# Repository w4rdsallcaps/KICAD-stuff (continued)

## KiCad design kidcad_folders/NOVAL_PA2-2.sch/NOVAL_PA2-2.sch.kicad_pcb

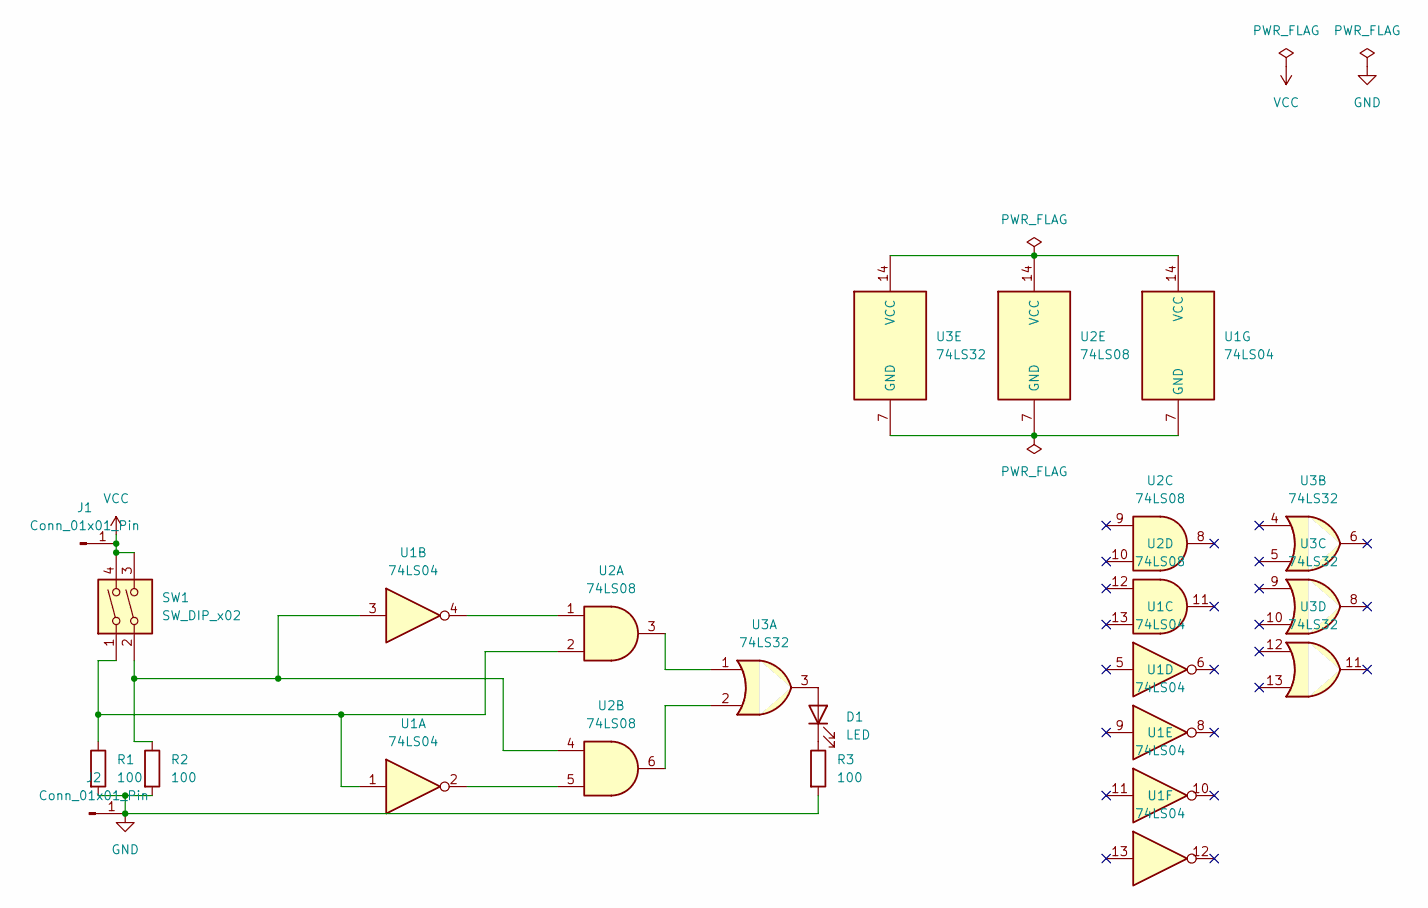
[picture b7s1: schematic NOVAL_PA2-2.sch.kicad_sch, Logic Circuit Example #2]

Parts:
D1: LED; LED_2512_6332Metric_Pad1.52x3.35mm_HandSolder
J1, J2: Conn_01x01_Pin; MountingHole_2.2mm_M2_DIN965_Pad
R1, R2, R3: 100; R_0508_1220Metric
SW1: SW_DIP_x02; SW_DIP_SPSTx02_Slide_9.78x7.26mm_W7.62mm_P2.54mm
U1: 74LS04; SOIC-14_3.9x8.7mm_P1.27mm
U2: 74LS08; SOIC-14_3.9x8.7mm_P1.27mm
U3: 74LS32; SOIC-14_3.9x8.7mm_P1.27mm

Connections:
GND: J2.1 (Pin_1_1), R1.2, R2.2, R3.2
unnamed: D1.2 (A), U3.3
unnamed: D1.1 (K), R3.1
unnamed: R1.1, SW1.1, U1.1, U2.2
unnamed: R2.1, SW1.2, U1.3, U2.4
unnamed: U1.2, U2.5
unnamed: U1.4, U2.1
unnamed: U1.7 (GND), U2.7 (GND), U3.7 (GND)
unnamed: U1.14 (VCC), U2.14 (VCC), U3.14 (VCC)
unnamed: U2.3, U3.1
unnamed: U2.6, U3.2
VCC: J1.1 (Pin_1_1), SW1.3, SW1.4

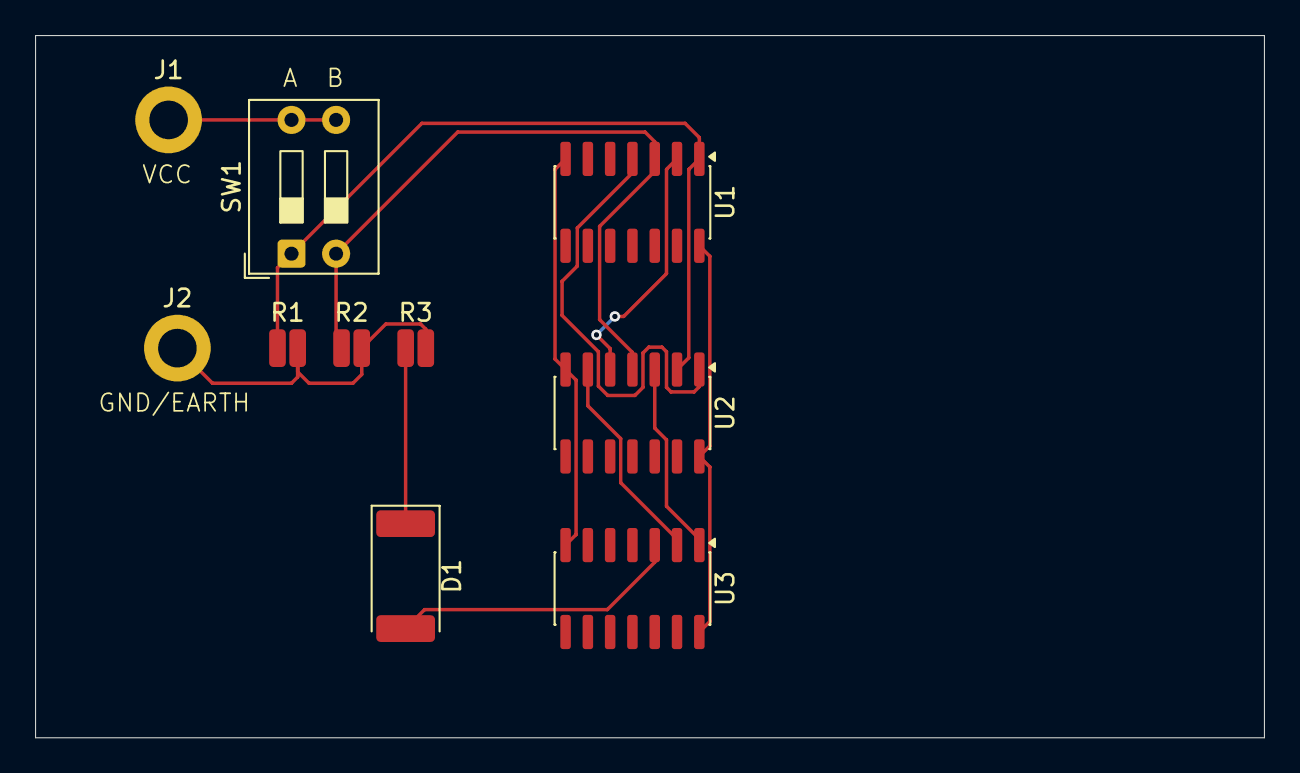
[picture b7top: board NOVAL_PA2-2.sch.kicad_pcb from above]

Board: 2 copper layers, 70.0 x 40.0 mm, 10 parts (0 on the bottom side), 12 nets.
